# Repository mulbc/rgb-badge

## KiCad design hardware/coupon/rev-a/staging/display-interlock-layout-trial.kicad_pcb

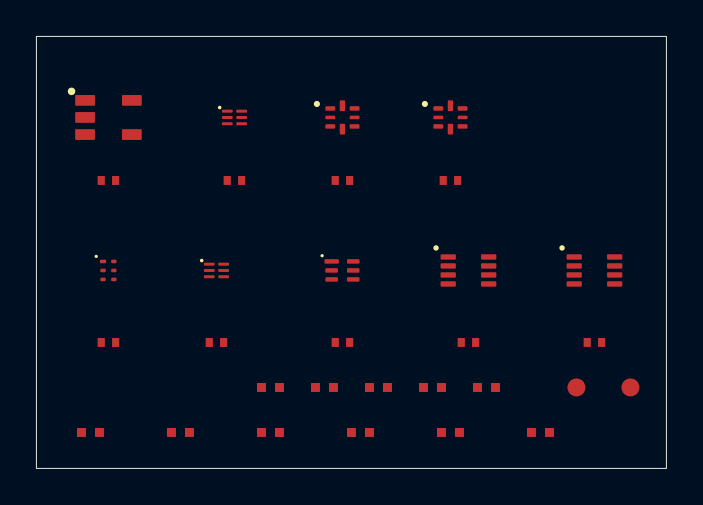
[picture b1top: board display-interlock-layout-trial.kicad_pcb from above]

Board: 2 copper layers, 35.0 x 24.0 mm, 31 parts (0 on the bottom side), 20 nets, no tracks yet.

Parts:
C66, C67, C68, C69, C70, C71, C72, C73, C74: 100n 16V X7R; C_Murata_GRM15_0402
R103: ERJ2RKF1001X; R_Panasonic_ERJ2_0402
R104, R105, R106: ERJ2RKF1002X; R_Panasonic_ERJ2_0402
R107, R108: ERJ2RKF1003X; R_Panasonic_ERJ2_0402
R109: ERJ2RKF1603X; R_Panasonic_ERJ2_0402
R110, R112: ERJ2RKF2002X; R_Panasonic_ERJ2_0402
R111: ERJ2RKF1963X; R_Panasonic_ERJ2_0402
R113: ERJ2RKF4701X; R_Panasonic_ERJ2_0402
TP13, TP14: TestPoint_Pad; TestPoint_Pad_D1.0mm
U47: TPS3823A-33DBVR; SOT23_TI_DBV0005A
U48: SN74LVC1G04DSFR; X2SON_TI_DSF0006A_1x1mm_P0.35mm
U49, U50: SN74LVC1G74RSER; UQFN_TI_RSE0008A_1.5x1.5mm_P0.5mm
U51: SN74LVC1G11DRYR; USON_TI_DRY0006A_1p45x1mm_P0p5mm
U52: SN74LVC1G08DSFR; X2SON_TI_DSF0006A_1x1mm_P0.35mm
U53: TLV6700DSER; WSON_TI_DSE0006A_1p5x1p5mm_P0p5mm
U54: SN74LVC2G00DCUR; VSSOP_TI_DCU0008A
U55: SN74LVC2G08DCUR; VSSOP_TI_DCU0008A

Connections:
+3V3_APP: C66.1, C67.1, C68.1, C69.1, C70.1, C71.1, C72.1, C73.1, C74.1, R104.1, R106.1, U47.3, U47.5, U48.6, U49.2, U49.7, U49.8, U50.7, U50.8, U51.5, U52.6, U53.2, U54.8, U55.8
APP_SUPERVISOR_OK: U47.1, U51.1
ARM_LATCH: U50.5, U55.1, U55.5
DISPLAY_ARM_CLK: R107.1, U50.1
DISPLAY_CLEAR_3: U51.4, U52.1
DISPLAY_CLEAR_OK: R108.1, U49.6, U50.6, U52.4
DISPLAY_ENABLE: R105.1, U52.2, U55.2
DISPLAY_HEARTBEAT: R103.1, U47.4, U48.2
GND: C66.2, C67.2, C68.2, C69.2, C70.2, C71.2, C72.2, C73.2, C74.2, R103.2, R105.2, R107.2, R108.2, R110.2, R112.2, R113.2, U47.2, U48.3, U49.4, U50.4, U51.2, U52.3, U53.5, U54.4, U55.4
HEARTBEAT_FALL_CLK: U48.4, U49.1
HEARTBEAT_SEEN: U49.5, U50.2
ROW_ARM: U54.5, U55.3
ROW_ENABLE_N_CANDIDATE: TP14.1, U54.3
ROW_ENABLE_REQ_N: R106.2, U54.1, U54.2
ROW_REQUEST: U54.6, U54.7
VLED: R109.1, R111.1, R113.1
VLED_ENABLE_CANDIDATE: TP13.1, U55.7
VLED_HIGH_SENSE: R111.2, R112.1, U53.3
VLED_LOW_SENSE: R109.2, R110.1, U53.4
VLED_WINDOW_OK: R104.2, U53.1, U53.6, U55.6

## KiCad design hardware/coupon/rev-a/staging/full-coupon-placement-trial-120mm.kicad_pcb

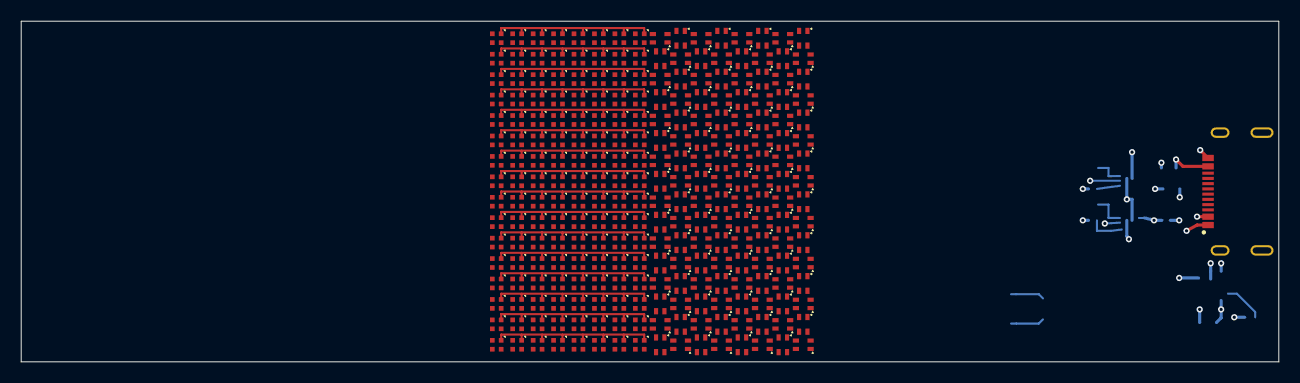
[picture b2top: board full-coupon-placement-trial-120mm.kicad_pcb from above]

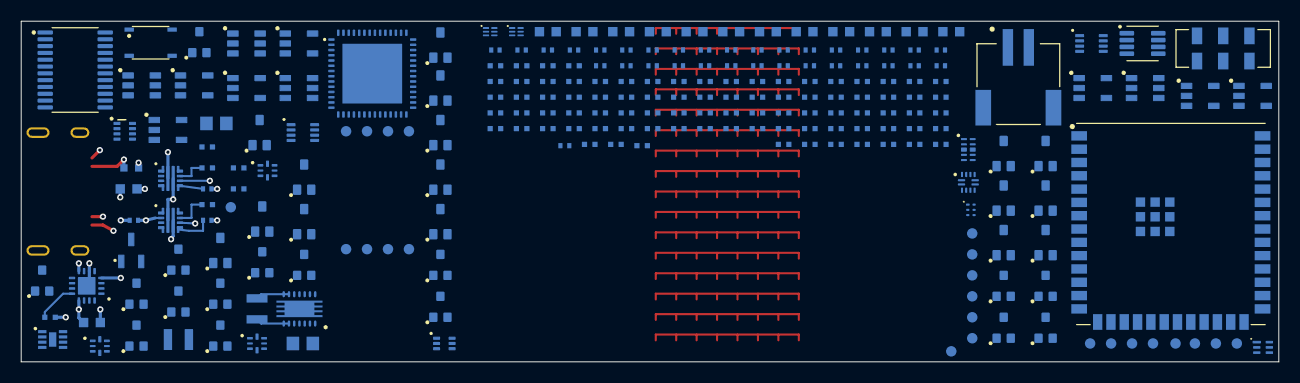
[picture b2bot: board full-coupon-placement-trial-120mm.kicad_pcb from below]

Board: 6 copper layers, 120.0 x 32.5 mm, 497 parts (240 on the bottom side), 188 nets.

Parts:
C1, C2, C4, C11, C17, C23, C24, C25, C36, C37, C38, C39, C50, C51, C55, C58, C59, C63, C64, C65, C66, C67, C68, C69, C70, C71, C72, C73, C74: 100n 16V X7R; C_Murata_GRM15_0402
C3, C32, C44, C45, C53, C54: 10u 6.3V X5R; C_Murata_GRM18_0603
C5, C30, C31, C52: 1u 10V X7S; C_Murata_GRM15_0402
C40, C41, C46, C47, C48, C49, C56, C61: 22u 10V X5R; C_Murata_GRM18_0603
C42, C43: 47u 6.3V X5R; C_Murata_GRM21_0805
C57, C62: 2.2n 50V C0G; C_Murata_GRM15_0402
C60: 1u 50V X7R; C_TDK_C1608_0603
D1, D2, D3, D4, D5, D6, D7, D8, D17, D18, D19, D20, D21, D22, D23, D24, D33, D34, D35, D36, D37, D38, D39, D40, D49, D50, D51, D52, D53, D54, D55, D56, D65, D66, D67, D68, D69, D70, D71, D72, D81, D82, D83, D84, D85, D86, D87, D88, D97, D98, D99, D100, D101, D102, D103, D104, D113, D114, D115, D116, D117, D118, D119, D120, D129, D130, D131, D132, D133, D134, D135, D136, D145, D146, D147, D148, D149, D150, D151, D152, D161, D162, D163, D164, D165, D166, D167, D168, D177, D178, D179, D180, D181, D182, D183, D184, D193, D194, D195, D196, D197, D198, D199, D200, D209, D210, D211, D212, D213, D214, D215, D216, D225, D226, D227, D228, D229, D230, D231, D232, D241, D242, D243, D244, D245, D246, D247, D248: EAST10105RGBA0; LED_Everlight_EAST10105RGBA0
D9, D10, D11, D12, D13, D14, D15, D16, D25, D26, D27, D28, D29, D30, D31, D32, D41, D42, D43, D44, D45, D46, D47, D48, D57, D58, D59, D60, D61, D62, D63, D64, D73, D74, D75, D76, D77, D78, D79, D80, D89, D90, D91, D92, D93, D94, D95, D96, D105, D106, D107, D108, D109, D110, D111, D112, D121, D122, D123, D124, D125, D126, D127, D128, D137, D138, D139, D140, D141, D142, D143, D144, D153, D154, D155, D156, D157, D158, D159, D160, D169, D170, D171, D172, D173, D174, D175, D176, D185, D186, D187, D188, D189, D190, D191, D192, D201, D202, D203, D204, D205, D206, D207, D208, D217, D218, D219, D220, D221, D222, D223, D224, D233, D234, D235, D236, D237, D238, D239, D240, D249, D250, D251, D252, D253, D254, D255, D256: QBLP1515A-RGB2A; LED_QTBrightek_QBLP1515A-RGB2A
J1: USB4505-03-0-A; USB_C_GCT_USB4505-03-0-A_MidMount
J2: S2B-PH-SM4-TB; JST_PH_S2B-PH-SM4-TB
L1: 1u 20%; L_Murata_DFE252012P
L2: 1.5u 20%; L_Murata_DFE252012P
Q1, Q2, Q3, Q4, Q5, Q6, Q7, Q8, Q9, Q10, Q11, Q12, Q13, Q14, Q15, Q16: DMP2066LSN-7; SC59_Diodes_DMP2066LSN
Q17, Q18, Q19, Q20, Q21, Q22, Q23, Q24, Q25, Q26, Q27, Q28, Q29, Q30, Q31, Q32: 2N7002K-7; SOT23_Diodes_2N7002K
R1: 39.2k 1%; R_Panasonic_ERJ2_0402
R2, R3, R4, R5, R22, R23, R24, R25, R26, R27, R28, R29, R30, R31, R32, R33, R34, R35, R36, R37, R38, R39, R40, R41, R42, R62, R76, R77, R78, R83, R87: 100k 1%; R_Panasonic_ERJ2_0402
R6, R7, R8, R9, R10, R11, R12, R13, R14, R15, R16, R17, R18, R19, R20, R21: 1k 1%; R_Panasonic_ERJ2_0402
R43, R44, R60, R61, R70, R88, R91, R98: 10k 1%; R_Panasonic_ERJ2_0402
R45, R46: 22R 1%; R_Panasonic_ERJ2_0402
R47: 499R 1%; R_Panasonic_ERJ2_0402
R63: 1M 1%; R_Panasonic_ERJ2_0402
R71: 887k 1%; R_Panasonic_ERJ2_0402
R75, R84, R85: 620k 1%; R_Panasonic_ERJ2_0402
R79, R80, R101, R102: 2.2k 1%; R_Panasonic_ERJ2_0402
R81: 511k 1%; R_Panasonic_ERJ2_0402
R82: 91k 1%; R_Panasonic_ERJ2_0402
R86: 180k 1%; R_Panasonic_ERJ2_0402
R89: 2.15k 1%; R_Panasonic_ERJ2_0402
R90: 14k 1%; R_Panasonic_ERJ2_0402
R92: 2.49k 0.1%; R_Panasonic_ERA2_0402
R93: 3.65k 0.1%; R_Panasonic_ERA2_0402
R94: 220k 1%; R_Panasonic_ERJ2_0402
R95: 270k 1%; R_Panasonic_ERJ2_0402
R96, R100: 3.32k 1%; R_Panasonic_ERJ2_0402
R97: 38.3k 1%; R_Panasonic_ERJ2_0402
R99: 390k 1%; R_Panasonic_ERJ2_0402
R103: ERJ2RKF1001X; R_Panasonic_ERJ2_0402
R104, R105, R106: ERJ2RKF1002X; R_Panasonic_ERJ2_0402
R107, R108: ERJ2RKF1003X; R_Panasonic_ERJ2_0402
R109: ERJ2RKF1603X; R_Panasonic_ERJ2_0402
R110, R112: ERJ2RKF2002X; R_Panasonic_ERJ2_0402
R111: ERJ2RKF1963X; R_Panasonic_ERJ2_0402
R113: ERJ2RKF4701X; R_Panasonic_ERJ2_0402
SW1: EVQP7J01P; SW_Panasonic_EVQP7J01P
SW2: JS202011JCQN; SW_CK_JS202011JCQN
TH1: 10k NTC; NTC_Murata_NCU15_0402
TP1: LED_SOUT; TestPoint_Pad_D1.0mm
TP2, TP3, TP4, TP5, TP6, TP7, TP8, TP9, TP10, TP11, TP12, TP13, TP14, TP34, TP35: TestPoint_Pad; TestPoint_Pad_D1.0mm
TP20: OUT1; TestPoint_Pad_D1.0mm
TP21: OUT2; TestPoint_Pad_D1.0mm
TP22: VBUS_VALID; TestPoint_Pad_D1.0mm
TP23: LOGIC_READY; TestPoint_Pad_D1.0mm
TP30: CHARGE_REQ; TestPoint_Pad_D1.0mm
TP31: EN1_RAW_N; TestPoint_Pad_D1.0mm
TP32: VBUS_CONNECTOR; TestPoint_Pad_D1.0mm
TP33: 5V_USB_BOUNDARY; TestPoint_Pad_D1.0mm
U1: TLC59581RTQT; QFN_TI_RTQ0056E_8x8mm_P0.5mm_EP5.7mm
U2: 74HC4514PW,118; TSSOP_Nexperia_SOT355-1_24
U3: ESP32-S3-WROOM-1U-N16R8; ESP32-S3-WROOM-1U
U11: SN74LVC1G04DBVR; SOT23_TI_DBV0005A
U17: SN74LVC1G11DBVR; SOT23_TI_DBV0006A
U23: SN74LVC1G06DBVR; SOT23_TI_DBV0005A
U24, U25: SN74LVC2G17DBVR; SOT23_TI_DBV0006A
U29: TPS70933DBVR; SOT23_TI_DBV0005A
U31: TUSB320LAIRWBR; X2QFN_TI_RWB0012A_1.6x1.6mm_P0.4mm
U32: TS3USB31ERSER; UQFN_TI_RSE0008A_1.5x1.5mm_P0.5mm
U33: TPD4E05U06DQAR; USON_TI_DQA0010A
U34: TPS3808G01DBVR; SOT23_TI_DBV0006A
U35: MAX17048G+T10; TDFN_Maxim_T822-3_2x2mm_P0.5mm_EP0.7x1.38mm
U36: TPS631000DRLR; SOT5X3_TI_DRL0008A
U37: TPS63020DSJT; VSON_TI_DSJ0014_4x3mm_P0.5mm_EP2.85x1.58mm
U38: 2.5V shunt; SOT23_TI_DBZ0003A
U39: TMP390A2DRLR; SOT563_TI_DRL0006A
U40, U42, U43: SN74AUP1G125DBVR; SOT23_TI_DBV0005A
U41: BQ24074RGTR; VQFN_TI_RGT0016C_3x3mm_P0.5mm_EP1.68mm
U44, U45: TPS259474ARPWR; VQFN_TI_RPW0010A_2x2mm_HotRod
U46: TCA9517ADGKR; VSSOP_TI_DGK0008A
U47: TPS3823A-33DBVR; SOT23_TI_DBV0005A
U48: SN74LVC1G04DSFR; X2SON_TI_DSF0006A_1x1mm_P0.35mm
U49, U50: SN74LVC1G74RSER; UQFN_TI_RSE0008A_1.5x1.5mm_P0.5mm
U51: SN74LVC1G11DRYR; USON_TI_DRY0006A_1p45x1mm_P0p5mm
U52: SN74LVC1G08DSFR; X2SON_TI_DSF0006A_1x1mm_P0.35mm
U53: TLV6700DSER; WSON_TI_DSE0006A_1p5x1p5mm_P0p5mm
U54: SN74LVC2G00DCUR; VSSOP_TI_DCU0008A
U55: SN74LVC2G08DCUR; VSSOP_TI_DCU0008A

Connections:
+3V3_APP: C1.1, C2.1, C3.1, C4.1, C37.1, C42.1, C43.1, C65.1, C66.1, C67.1, C68.1, C69.1, C70.1, C71.1, C72.1, C73.1, C74.1, R42.1, R43.1, R44.1, R79.1, R80.1, R81.1, R104.1, R106.1, TP8.1, U1.43, U2.1, U2.24, U3.2, U32.8, U36.1, U46.5, U46.8, U47.3, U47.5, U48.6, U49.2, U49.7, U49.8, U50.7, U50.8, U51.5, U52.6, U53.2, U54.8, U55.8
+3V3_USB: C11.1, C17.1, C23.1, C24.1, C25.1, C32.1, C36.1, C38.1, C50.1, C51.1, C58.1, C59.1, R60.2, R61.2, R70.1, R75.1, R77.1, R78.1, R91.1, R94.1, U11.5, U17.5, U23.5, U24.5, U25.5, U29.5, U31.12, U34.3, U34.6, U39.5, U40.5, U42.5, U43.5
+5V_USB: C30.1, C31.1, C55.1, C61.1, TP33.1, U29.1, U44.5, U45.6
+BAT_GAUGE_SW: C39.1, C64.1, R101.1, R102.1, SW2.6, U35.2, U35.3, U46.1
+BAT_PROTECTED_DRAFT: C53.1, J2.1, SW2.5, U41.2, U41.3
+SYS_APP_IN_DRAFT: C40.1, C41.1, C44.1, C45.1, C54.1, C63.1, SW2.2, U36.4, U37.1, U37.10, U37.11, U41.10, U41.11
APP_3V3_FB: R81.2, R82.1, U36.8
APP_ON_SW_DRAFT: R83.1, SW2.3, U36.5
APP_SUPERVISOR_OK: U47.1, U51.1
ARM_LATCH: U50.5, U55.1, U55.5
CHARGER_EN2: R88.2, U38.1, U41.5
CHARGER_GATE_EN: R94.2, R95.1, TP35.1, U40.4, U42.4, U43.4, U44.1
CHARGER_ILIM: R93.1, U41.12
CHARGER_IN_DRAFT: C52.1, C56.1, R88.1, U41.13, U44.6
CHARGER_ISET: R92.1, U41.16
CHARGER_TS: TH1.1, TP34.1, U41.1
COL_00_B: D1.3, D17.3, D33.3, D49.3, D65.3, D81.3, D97.3, D113.3, D129.3, D145.3, D161.3, D177.3, D193.3, D209.3, D225.3, D241.3, U1.10
COL_00_G: D1.4, D17.4, D33.4, D49.4, D65.4, D81.4, D97.4, D113.4, D129.4, D145.4, D161.4, D177.4, D193.4, D209.4, D225.4, D241.4, U1.9
COL_00_R: D1.2, D17.2, D33.2, D49.2, D65.2, D81.2, D97.2, D113.2, D129.2, D145.2, D161.2, D177.2, D193.2, D209.2, D225.2, D241.2, U1.8
COL_01_B: D2.3, D18.3, D34.3, D50.3, D66.3, D82.3, D98.3, D114.3, D130.3, D146.3, D162.3, D178.3, D194.3, D210.3, D226.3, D242.3, U1.13
COL_01_G: D2.4, D18.4, D34.4, D50.4, D66.4, D82.4, D98.4, D114.4, D130.4, D146.4, D162.4, D178.4, D194.4, D210.4, D226.4, D242.4, U1.12
COL_01_R: D2.2, D18.2, D34.2, D50.2, D66.2, D82.2, D98.2, D114.2, D130.2, D146.2, D162.2, D178.2, D194.2, D210.2, D226.2, D242.2, U1.11
COL_02_B: D3.3, D19.3, D35.3, D51.3, D67.3, D83.3, D99.3, D115.3, D131.3, D147.3, D163.3, D179.3, D195.3, D211.3, D227.3, D243.3, U1.16
COL_02_G: D3.4, D19.4, D35.4, D51.4, D67.4, D83.4, D99.4, D115.4, D131.4, D147.4, D163.4, D179.4, D195.4, D211.4, D227.4, D243.4, U1.15
COL_02_R: D3.2, D19.2, D35.2, D51.2, D67.2, D83.2, D99.2, D115.2, D131.2, D147.2, D163.2, D179.2, D195.2, D211.2, D227.2, D243.2, U1.14
COL_03_B: D4.3, D20.3, D36.3, D52.3, D68.3, D84.3, D100.3, D116.3, D132.3, D148.3, D164.3, D180.3, D196.3, D212.3, D228.3, D244.3, U1.19
COL_03_G: D4.4, D20.4, D36.4, D52.4, D68.4, D84.4, D100.4, D116.4, D132.4, D148.4, D164.4, D180.4, D196.4, D212.4, D228.4, D244.4, U1.18
COL_03_R: D4.2, D20.2, D36.2, D52.2, D68.2, D84.2, D100.2, D116.2, D132.2, D148.2, D164.2, D180.2, D196.2, D212.2, D228.2, D244.2, U1.17
COL_04_B: D5.3, D21.3, D37.3, D53.3, D69.3, D85.3, D101.3, D117.3, D133.3, D149.3, D165.3, D181.3, D197.3, D213.3, D229.3, D245.3, U1.22
COL_04_G: D5.4, D21.4, D37.4, D53.4, D69.4, D85.4, D101.4, D117.4, D133.4, D149.4, D165.4, D181.4, D197.4, D213.4, D229.4, D245.4, U1.21
COL_04_R: D5.2, D21.2, D37.2, D53.2, D69.2, D85.2, D101.2, D117.2, D133.2, D149.2, D165.2, D181.2, D197.2, D213.2, D229.2, D245.2, U1.20
COL_05_B: D6.3, D22.3, D38.3, D54.3, D70.3, D86.3, D102.3, D118.3, D134.3, D150.3, D166.3, D182.3, D198.3, D214.3, D230.3, D246.3, U1.25
COL_05_G: D6.4, D22.4, D38.4, D54.4, D70.4, D86.4, D102.4, D118.4, D134.4, D150.4, D166.4, D182.4, D198.4, D214.4, D230.4, D246.4, U1.24
COL_05_R: D6.2, D22.2, D38.2, D54.2, D70.2, D86.2, D102.2, D118.2, D134.2, D150.2, D166.2, D182.2, D198.2, D214.2, D230.2, D246.2, U1.23
COL_06_B: D7.3, D23.3, D39.3, D55.3, D71.3, D87.3, D103.3, D119.3, D135.3, D151.3, D167.3, D183.3, D199.3, D215.3, D231.3, D247.3, U1.32
COL_06_G: D7.4, D23.4, D39.4, D55.4, D71.4, D87.4, D103.4, D119.4, D135.4, D151.4, D167.4, D183.4, D199.4, D215.4, D231.4, D247.4, U1.31
COL_06_R: D7.2, D23.2, D39.2, D55.2, D71.2, D87.2, D103.2, D119.2, D135.2, D151.2, D167.2, D183.2, D199.2, D215.2, D231.2, D247.2, U1.30
COL_07_B: D8.3, D24.3, D40.3, D56.3, D72.3, D88.3, D104.3, D120.3, D136.3, D152.3, D168.3, D184.3, D200.3, D216.3, D232.3, D248.3, U1.35
COL_07_G: D8.4, D24.4, D40.4, D56.4, D72.4, D88.4, D104.4, D120.4, D136.4, D152.4, D168.4, D184.4, D200.4, D216.4, D232.4, D248.4, U1.34
COL_07_R: D8.2, D24.2, D40.2, D56.2, D72.2, D88.2, D104.2, D120.2, D136.2, D152.2, D168.2, D184.2, D200.2, D216.2, D232.2, D248.2, U1.33
COL_08_B: D9.2, D25.2, D41.2, D57.2, D73.2, D89.2, D105.2, D121.2, D137.2, D153.2, D169.2, D185.2, D201.2, D217.2, D233.2, D249.2, U1.38
COL_08_G: D9.3, D25.3, D41.3, D57.3, D73.3, D89.3, D105.3, D121.3, D137.3, D153.3, D169.3, D185.3, D201.3, D217.3, D233.3, D249.3, U1.37
COL_08_R: D9.4, D25.4, D41.4, D57.4, D73.4, D89.4, D105.4, D121.4, D137.4, D153.4, D169.4, D185.4, D201.4, D217.4, D233.4, D249.4, U1.36
COL_09_B: D10.2, D26.2, D42.2, D58.2, D74.2, D90.2, D106.2, D122.2, D138.2, D154.2, D170.2, D186.2, D202.2, D218.2, D234.2, D250.2, U1.41
COL_09_G: D10.3, D26.3, D42.3, D58.3, D74.3, D90.3, D106.3, D122.3, D138.3, D154.3, D170.3, D186.3, D202.3, D218.3, D234.3, D250.3, U1.40
COL_09_R: D10.4, D26.4, D42.4, D58.4, D74.4, D90.4, D106.4, D122.4, D138.4, D154.4, D170.4, D186.4, D202.4, D218.4, D234.4, D250.4, U1.39
COL_10_B: D11.2, D27.2, D43.2, D59.2, D75.2, D91.2, D107.2, D123.2, D139.2, D155.2, D171.2, D187.2, D203.2, D219.2, D235.2, D251.2, U1.46
COL_10_G: D11.3, D27.3, D43.3, D59.3, D75.3, D91.3, D107.3, D123.3, D139.3, D155.3, D171.3, D187.3, D203.3, D219.3, D235.3, D251.3, U1.45
COL_10_R: D11.4, D27.4, D43.4, D59.4, D75.4, D91.4, D107.4, D123.4, D139.4, D155.4, D171.4, D187.4, D203.4, D219.4, D235.4, D251.4, U1.44
COL_11_B: D12.2, D28.2, D44.2, D60.2, D76.2, D92.2, D108.2, D124.2, D140.2, D156.2, D172.2, D188.2, D204.2, D220.2, D236.2, D252.2, U1.49
COL_11_G: D12.3, D28.3, D44.3, D60.3, D76.3, D92.3, D108.3, D124.3, D140.3, D156.3, D172.3, D188.3, D204.3, D220.3, D236.3, D252.3, U1.48
COL_11_R: D12.4, D28.4, D44.4, D60.4, D76.4, D92.4, D108.4, D124.4, D140.4, D156.4, D172.4, D188.4, D204.4, D220.4, D236.4, D252.4, U1.47
COL_12_B: D13.2, D29.2, D45.2, D61.2, D77.2, D93.2, D109.2, D125.2, D141.2, D157.2, D173.2, D189.2, D205.2, D221.2, D237.2, D253.2, U1.52
COL_12_G: D13.3, D29.3, D45.3, D61.3, D77.3, D93.3, D109.3, D125.3, D141.3, D157.3, D173.3, D189.3, D205.3, D221.3, D237.3, D253.3, U1.51
COL_12_R: D13.4, D29.4, D45.4, D61.4, D77.4, D93.4, D109.4, D125.4, D141.4, D157.4, D173.4, D189.4, D205.4, D221.4, D237.4, D253.4, U1.50
COL_13_B: D14.2, D30.2, D46.2, D62.2, D78.2, D94.2, D110.2, D126.2, D142.2, D158.2, D174.2, D190.2, D206.2, D222.2, D238.2, D254.2, U1.55
COL_13_G: D14.3, D30.3, D46.3, D62.3, D78.3, D94.3, D110.3, D126.3, D142.3, D158.3, D174.3, D190.3, D206.3, D222.3, D238.3, D254.3, U1.54
COL_13_R: D14.4, D30.4, D46.4, D62.4, D78.4, D94.4, D110.4, D126.4, D142.4, D158.4, D174.4, D190.4, D206.4, D222.4, D238.4, D254.4, U1.53
COL_14_B: D15.2, D31.2, D47.2, D63.2, D79.2, D95.2, D111.2, D127.2, D143.2, D159.2, D175.2, D191.2, D207.2, D223.2, D239.2, D255.2, U1.4
COL_14_G: D15.3, D31.3, D47.3, D63.3, D79.3, D95.3, D111.3, D127.3, D143.3, D159.3, D175.3, D191.3, D207.3, D223.3, D239.3, D255.3, U1.3
COL_14_R: D15.4, D31.4, D47.4, D63.4, D79.4, D95.4, D111.4, D127.4, D143.4, D159.4, D175.4, D191.4, D207.4, D223.4, D239.4, D255.4, U1.2
COL_15_B: D16.2, D32.2, D48.2, D64.2, D80.2, D96.2, D112.2, D128.2, D144.2, D160.2, D176.2, D192.2, D208.2, D224.2, D240.2, D256.2, U1.7
COL_15_G: D16.3, D32.3, D48.3, D64.3, D80.3, D96.3, D112.3, D128.3, D144.3, D160.3, D176.3, D192.3, D208.3, D224.3, D240.3, D256.3, U1.6
COL_15_R: D16.4, D32.4, D48.4, D64.4, D80.4, D96.4, D112.4, D128.4, D144.4, D160.4, D176.4, D192.4, D208.4, D224.4, D240.4, D256.4, U1.5
DISPLAY_ARM_CLK: R107.1, U3.9, U50.1
DISPLAY_CLEAR_3: U51.4, U52.1
DISPLAY_CLEAR_OK: R108.1, U49.6, U50.6, U52.4
DISPLAY_ENABLE: R105.1, TP10.1, U3.17, U52.2, U55.2
DISPLAY_HEARTBEAT: R103.1, U3.8, U47.4, U48.2
E0_DVDT: C62.1, U45.7
E0_EN: R99.2, U45.1
E0_ILM: R100.1, U45.9
E0_OVLO: R97.2, R98.1, U45.2
E1_DVDT: C57.1, U44.7
E1_ILM: R96.1, U44.9
ESP_EN: C5.1, R43.2, TP2.1, U3.3, U51.3
GAUGE_I2C_SCL: R102.2, U35.7, U46.2
GAUGE_I2C_SDA: R101.2, U35.8, U46.3
GND: C1.2, C2.2, C3.2, C4.2, C5.2, C11.2, C17.2, C23.2, C24.2, C25.2, C30.2, C31.2, C32.2, C36.2, C37.2, C38.2, C39.2, C40.2, C41.2, C42.2, C43.2, C44.2, C45.2, C46.2, C47.2, C48.2, C49.2, C50.2, C51.2, C52.2, C53.2, C54.2, C55.2, C56.2, C57.2, C58.2, C59.2, C60.2, C61.2, C62.2, C63.2, C64.2, C65.2, C66.2, C67.2, C68.2, C69.2, C70.2, C71.2, C72.2, C73.2, C74.2, J1.A1_B12, J1.B1_A12, J1.S1, J2.2, Q17.2, Q18.2, Q19.2, Q20.2, Q21.2, Q22.2, Q23.2, Q24.2, Q25.2, Q26.2, Q27.2, Q28.2, Q29.2, Q30.2, Q31.2, Q32.2, R1.2, R2.2, R3.2, R4.2, R5.2, R22.2, R23.2, R24.2, R25.2, R26.2, R27.2, R28.2, R29.2, R30.2, R31.2, R32.2, R33.2, R34.2, R35.2, R36.2, R37.2, R38.2, R39.2, R40.2, R41.2, R62.2, R63.2, R76.2, R82.2, R83.2, R86.2, R87.2, R89.2, R90.2, R92.2, R93.2, R95.2, R96.2, R98.2, R100.2, R103.2, R105.2, R107.2, R108.2, R110.2, R112.2, R113.2, SW1.2, TH1.2, TP9.1, U1.56, U1.57, U2.12, U3.1, U3.40, U3.41, U11.3, U17.2, U23.3, U24.2, U25.2, U29.2, U31.3, U31.10, U31.11, U32.1, U32.4, U33.3, U33.8, U34.2, U35.1, U35.4, U35.6, U35.9, U36.6, U36.7, U37.2, U37.13, U37.15, U38.2, U38.3, U39.3, U40.2, U40.3, U41.4, U41.6, U41.8, U41.17, U42.2, U42.3, U43.2, U43.3, U44.2, U44.8, U45.8, U46.4, U47.2, U48.3, U49.4, U50.4, U51.2, U52.3, U53.5, U54.4, U55.4
HEARTBEAT_FALL_CLK: U48.4, U49.1
HEARTBEAT_SEEN: U49.5, U50.2
LED_GCLK: R5.1, TP6.1, U1.29, U3.21
LED_IREF: R1.1, U1.1
LED_LAT: R4.1, U1.27, U3.18
LED_SCLK: R3.1, U1.28, U3.20
LED_SIN: R2.1, U1.26, U3.19
LED_SOUT: TP1.1, U1.42, U3.22
MODE_BOOT_N: R44.2, SW1.1, TP3.1, U3.27, U51.6
unnamed: L2.1, U37.8, U37.9
unnamed: L2.2, U37.6, U37.7
unnamed: L1.1, U36.3
unnamed: L1.2, U36.2
ROW_00_A: D1.1, D2.1, D3.1, D4.1, D5.1, D6.1, D7.1, D8.1, D9.1, D10.1, D11.1, D12.1, D13.1, D14.1, D15.1, D16.1, Q1.3
ROW_01_A: D17.1, D18.1, D19.1, D20.1, D21.1, D22.1, D23.1, D24.1, D25.1, D26.1, D27.1, D28.1, D29.1, D30.1, D31.1, D32.1, Q2.3
ROW_02_A: D33.1, D34.1, D35.1, D36.1, D37.1, D38.1, D39.1, D40.1, D41.1, D42.1, D43.1, D44.1, D45.1, D46.1, D47.1, D48.1, Q3.3
ROW_03_A: D49.1, D50.1, D51.1, D52.1, D53.1, D54.1, D55.1, D56.1, D57.1, D58.1, D59.1, D60.1, D61.1, D62.1, D63.1, D64.1, Q4.3
ROW_04_A: D65.1, D66.1, D67.1, D68.1, D69.1, D70.1, D71.1, D72.1, D73.1, D74.1, D75.1, D76.1, D77.1, D78.1, D79.1, D80.1, Q5.3
ROW_05_A: D81.1, D82.1, D83.1, D84.1, D85.1, D86.1, D87.1, D88.1, D89.1, D90.1, D91.1, D92.1, D93.1, D94.1, D95.1, D96.1, Q6.3
ROW_06_A: D97.1, D98.1, D99.1, D100.1, D101.1, D102.1, D103.1, D104.1, D105.1, D106.1, D107.1, D108.1, D109.1, D110.1, D111.1, D112.1, Q7.3
ROW_07_A: D113.1, D114.1, D115.1, D116.1, D117.1, D118.1, D119.1, D120.1, D121.1, D122.1, D123.1, D124.1, D125.1, D126.1, D127.1, D128.1, Q8.3
ROW_08_A: D129.1, D130.1, D131.1, D132.1, D133.1, D134.1, D135.1, D136.1, D137.1, D138.1, D139.1, D140.1, D141.1, D142.1, D143.1, D144.1, Q9.3
ROW_09_A: D145.1, D146.1, D147.1, D148.1, D149.1, D150.1, D151.1, D152.1, D153.1, D154.1, D155.1, D156.1, D157.1, D158.1, D159.1, D160.1, Q10.3
ROW_10_A: D161.1, D162.1, D163.1, D164.1, D165.1, D166.1, D167.1, D168.1, D169.1, D170.1, D171.1, D172.1, D173.1, D174.1, D175.1, D176.1, Q11.3
ROW_11_A: D177.1, D178.1, D179.1, D180.1, D181.1, D182.1, D183.1, D184.1, D185.1, D186.1, D187.1, D188.1, D189.1, D190.1, D191.1, D192.1, Q12.3
ROW_12_A: D193.1, D194.1, D195.1, D196.1, D197.1, D198.1, D199.1, D200.1, D201.1, D202.1, D203.1, D204.1, D205.1, D206.1, D207.1, D208.1, Q13.3
ROW_13_A: D209.1, D210.1, D211.1, D212.1, D213.1, D214.1, D215.1, D216.1, D217.1, D218.1, D219.1, D220.1, D221.1, D222.1, D223.1, D224.1, Q14.3
ROW_14_A: D225.1, D226.1, D227.1, D228.1, D229.1, D230.1, D231.1, D232.1, D233.1, D234.1, D235.1, D236.1, D237.1, D238.1, D239.1, D240.1, Q15.3
ROW_15_A: D241.1, D242.1, D243.1, D244.1, D245.1, D246.1, D247.1, D248.1, D249.1, D250.1, D251.1, D252.1, D253.1, D254.1, D255.1, D256.1, Q16.3
ROW_A0: R38.1, U2.2, U3.4
ROW_A1: R39.1, U2.3, U3.5
ROW_A2: R40.1, U2.21, U3.6
ROW_A3: R41.1, U2.22, U3.7
ROW_ARM: U54.5, U55.3
ROW_ENABLE_N: R42.2, U2.23
ROW_ENABLE_N_CANDIDATE: TP14.1, U54.3
ROW_ENABLE_REQ_N: R106.2, TP7.1, U3.12, U54.1, U54.2
ROW_GATE_00: Q1.1, Q17.3, R6.2
ROW_GATE_01: Q2.1, Q18.3, R7.2
ROW_GATE_02: Q3.1, Q19.3, R8.2
ROW_GATE_03: Q4.1, Q20.3, R9.2
ROW_GATE_04: Q5.1, Q21.3, R10.2
ROW_GATE_05: Q6.1, Q22.3, R11.2
ROW_GATE_06: Q7.1, Q23.3, R12.2
ROW_GATE_07: Q8.1, Q24.3, R13.2
ROW_GATE_08: Q9.1, Q25.3, R14.2
ROW_GATE_09: Q10.1, Q26.3, R15.2
ROW_GATE_10: Q11.1, Q27.3, R16.2
ROW_GATE_11: Q12.1, Q28.3, R17.2
ROW_GATE_12: Q13.1, Q29.3, R18.2
ROW_GATE_13: Q14.1, Q30.3, R19.2
ROW_GATE_14: Q15.1, Q31.3, R20.2
ROW_GATE_15: Q16.1, Q32.3, R21.2
ROW_REQUEST: U54.6, U54.7
ROW_SEL_00: Q17.1, R22.1, U2.11
ROW_SEL_01: Q18.1, R23.1, U2.9
ROW_SEL_02: Q19.1, R24.1, U2.10
ROW_SEL_03: Q20.1, R25.1, U2.8
ROW_SEL_04: Q21.1, R26.1, U2.7
ROW_SEL_05: Q22.1, R27.1, U2.6
ROW_SEL_06: Q23.1, R28.1, U2.5
ROW_SEL_07: Q24.1, R29.1, U2.4
ROW_SEL_08: Q25.1, R30.1, U2.18
ROW_SEL_09: Q26.1, R31.1, U2.17
ROW_SEL_10: Q27.1, R32.1, U2.20
ROW_SEL_11: Q28.1, R33.1, U2.19
ROW_SEL_12: Q29.1, R34.1, U2.14
ROW_SEL_13: Q30.1, R35.1, U2.13
ROW_SEL_14: Q31.1, R36.1, U2.16
ROW_SEL_15: Q32.1, R37.1, U2.15
SYS_I2C_SCL: R80.2, TP12.1, U3.11, U46.7
SYS_I2C_SDA: R79.2, TP11.1, U3.10, U46.6
TEMP_OK: R91.2, U39.4, U39.6, U40.1
TMP_COLD_SET: R90.1, U39.2
TMP_HOT_SET: R89.1, U39.1
UART0_RX: TP5.1, U3.36
UART0_TX: R47.2, TP4.1
UART0_TX_RAW: R47.1, U3.37
USB_CC1: J1.A5, U31.1, U33.4
USB_CC2: J1.B5, U31.2, U33.5
USB_CC_HIGH: U11.4, U17.6
USB_CHARGE_REQ: TP30.1, U17.4, U23.2, U42.1
USB_CONN_DM: J1.A7, J1.B7, U32.5, U33.2
USB_CONN_DP: J1.A6, J1.B6, U32.3, U33.1
USB_D+: R46.2, U32.2
USB_D-: R45.2, U32.6
USB_DN_MCU: R45.1, U3.13
USB_DP_MCU: R46.1, U3.14
USB_EN1_RAW_N: R70.2, TP31.1, U23.4
USB_LOGIC_CT: R77.2, U34.4
USB_LOGIC_READY: U17.3, U25.4
USB_LOGIC_SENSE: R75.2, R76.1, U34.5
USB_OUT1: U11.2, U24.6
USB_OUT2: TP21.1, U24.4
USB_RAW_LOGIC_READY: R63.1, R78.2, TP23.1, U25.3, U34.1, U43.1
USB_RAW_OUT1: R60.1, TP20.1, U24.1, U31.7
USB_RAW_OUT2: R61.1, U24.3, U31.8
USB_RAW_VBUS_VALID: R62.1, TP22.1, U25.1
USB_VBUS_DET: R71.2, U31.4
USB_VBUS_VALID: U17.1, U25.6
VBUS_CONNECTOR: C60.1, J1.A4_B9, J1.B4_A9, R71.1, R97.1, R99.1, TP32.1, U45.5
VLED: C46.1, C47.1, C48.1, C49.1, Q1.2, Q2.2, Q3.2, Q4.2, Q5.2, Q6.2, Q7.2, Q8.2, Q9.2, Q10.2, Q11.2, Q12.2, Q13.2, Q14.2, Q15.2, Q16.2, R6.1, R7.1, R8.1, R9.1, R10.1, R11.1, R12.1, R13.1, R14.1, R15.1, R16.1, R17.1, R18.1, R19.1, R20.1, R21.1, R84.1, R109.1, R111.1, R113.1, U37.4, U37.5
VLED_ENABLE_CANDIDATE: TP13.1, U55.7
VLED_ENABLE_DRAFT: R87.1, U37.12
VLED_FB: R85.2, R86.1, U37.3
VLED_FB_TOP_MID: R84.2, R85.1
VLED_HIGH_SENSE: R111.2, R112.1, U53.3
VLED_LOW_SENSE: R109.2, R110.1, U53.4
VLED_WINDOW_OK: R104.2, U53.1, U53.6, U55.6

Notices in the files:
parts and their libraries:
Manufacturer range-based reflow land pattern; SPDX-License-Identifier: CERN-OHL-S-2.0
Bare 1.0 mm copper probe pad; no purchased component or solder paste. SPDX-License-Identifier: CERN-OHL-S-2.0
TI DBV0005A SOT-23-5 manufacturer land pattern; SPDX-License-Identifier: CERN-OHL-S-2.0
